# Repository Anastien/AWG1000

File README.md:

**AWG1000** is a an open source  (GPL-3.0 License) dual-channel arbitrary waveform generators with a 120MHz bandwidth, 1.2GSa/s sampling rate and 16-bit vertical resolution.

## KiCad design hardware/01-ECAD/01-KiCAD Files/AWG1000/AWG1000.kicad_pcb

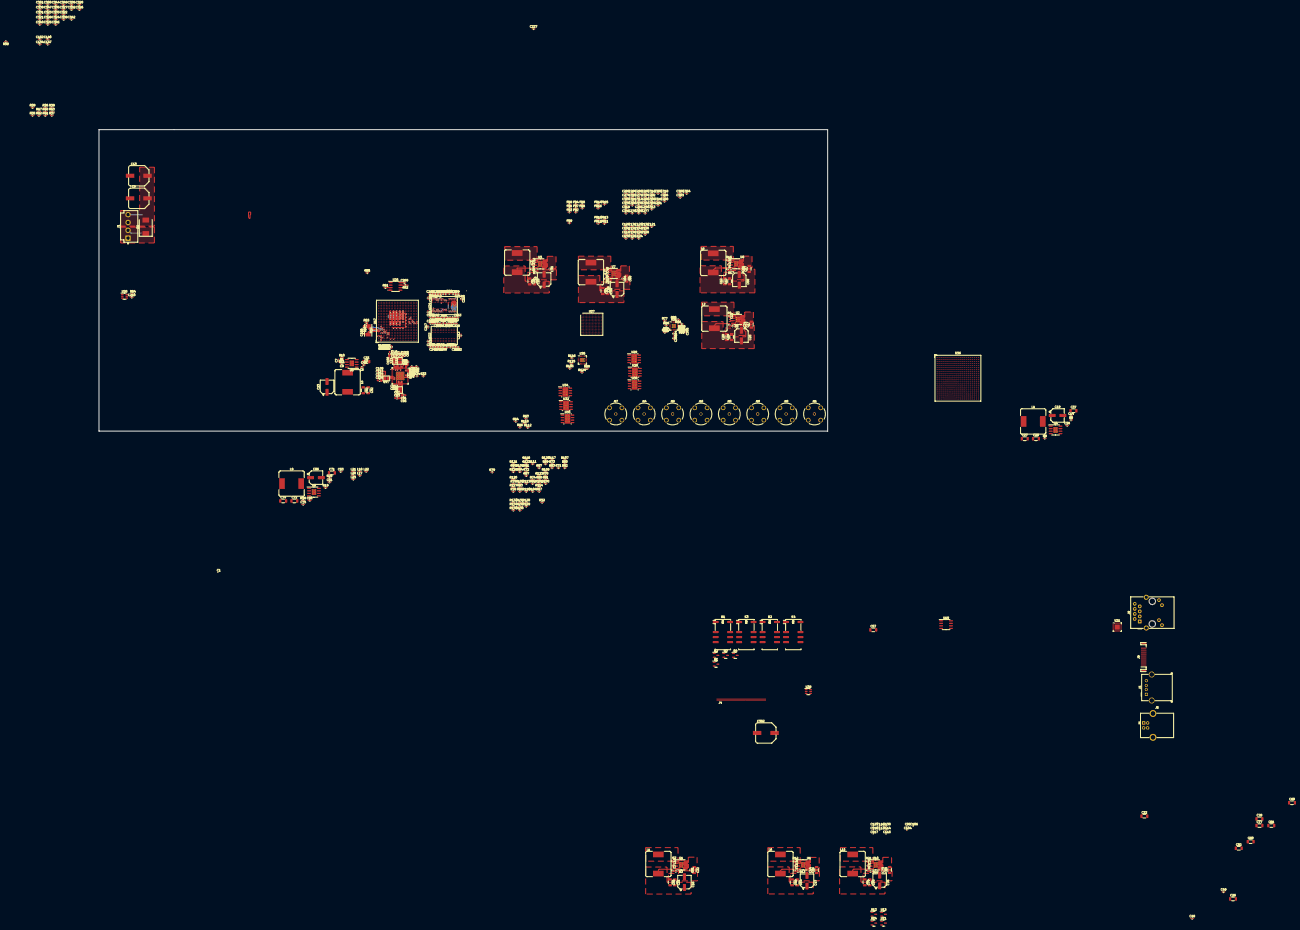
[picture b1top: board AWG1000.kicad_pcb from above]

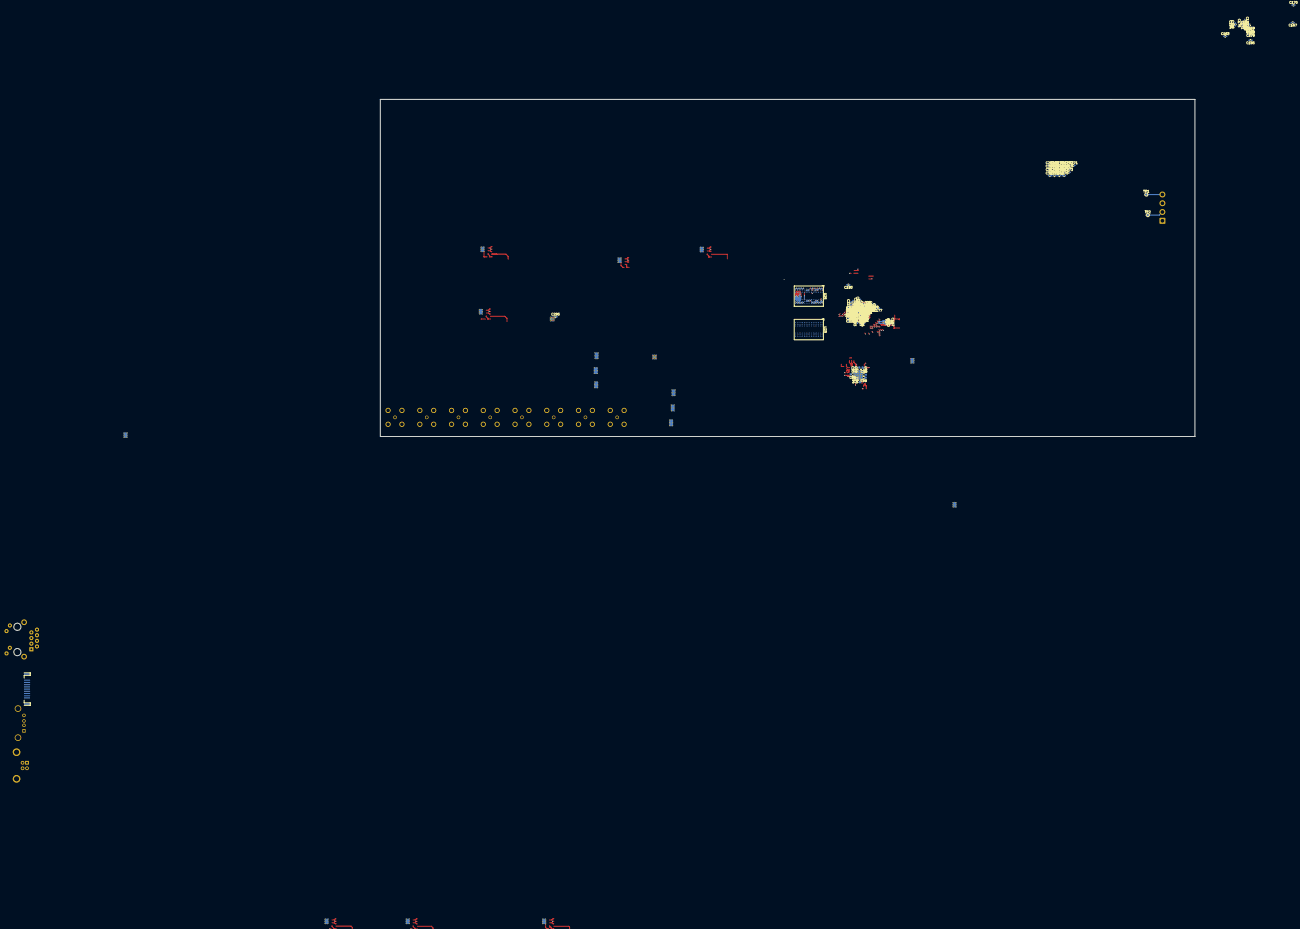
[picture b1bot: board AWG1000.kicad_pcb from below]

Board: 8 copper layers, 368.3 x 152.4 mm, 590 parts (113 on the bottom side), 374 nets.

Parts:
C1, C2, C3, C4, C15, C41, C45, C56, C95, C104, C106, C113, C114, C115, C116, C117, C118, C127, C130, C157, C158, C159, C164: 4.7uF; C0402_L
C6, C7, C9, C10, C11, C12, C14, C40, C49, C49#2, C49#3, C50, C51, C52, C53, C70: 0.47uF; R_0402_1005Metric_Pad0.72x0.64mm_HandSolder
C8, C13, C352: 220uF; EEE-FK1H221GP
C16, C18, C19, C20, C23, C47, C55, C58, C66, C76: 33uF; CP_Elec_6.3x7.7
C17, C21, C22, C22#2, C25, C26, C27, C28, C29, C30, C32, C33, C34, C36, C37, C39, C42, C48, C54, C57, C57#2, C59, C60, C62, C63, C65, C67, C68, C69, C71, C72, C74, C77, C78, C79, C80, C81, C82: 10uF; C_1206_3216Metric
C24, C31, C35, C38, C43, C44, C61, C64, C73, C75, C102, C109, C111, C112, C135, C136, C138, C139, C141, C142, C144, C145, C149, C150, C153, C154, C155, C156, C161, C162, C163, C165, C166, C168, C169, C171, C172, C174, C175, C178, C179, C180, C181, C182, C183, C184, C185, C190, C191, C192, C193, C194, C195, C196, C197, C198, C199, C200, C201, C202, C203, C204, C205, C206, C207, C208, C209, C210, C219, C220, C221, C222, C223, C224, C225, C226, C227, C228, C229, C230, C231, C232, C233, C234, C235, C236, C237, C238, C239, C240, C241, C242, C243, C244, C245, C246, C247, C248, C249, C250, C251, C252, C253, C254, C255, C256, C257, C258, C259, C260, C261, C262, C263, C264, C265, C266, C267, C268, C269, C270, C271, C272, C273, C275, C276, C287, C289, C290, C292, C293, C294, C296, C297, C310, C312, C317, C329, C343, C349: 220nF; R_0402_1005Metric_Pad0.72x0.64mm_HandSolder
C83, C84, C85, C86, C87, C88, C89, C90, C91, C92, C93, C94, C96, C97, C98, C99, C100, C101, C103, C105, C107, C108, C110: 22uF; C_0603_1608Metric_Pad1.08x0.95mm_HandSolder
C119, C120, C121, C122, C123, C124, C125, C126, C128, C129, C131, C132, C313, C353, C354, C355: 0.1uF; R_0402_1005Metric_Pad0.72x0.64mm_HandSolder
C133, C134, C140, C146, C147, C152, C160, C167, C170, C173, C176, C177, C186, C187, C188, C189, C211, C212, C213, C214, C215, C216, C217, C218, C295, C308, C320, C321, C322, C323, C324, C325, C326, C327, C328, C330, C331, C332, C333, C335, C336, C338, C340, C342, C344, C345, C347, C348, C350, C351: 22uF; R_0402_1005Metric_Pad0.72x0.64mm_HandSolder
C137, C143, C148, C151: 0.22uF; R_0402_1005Metric_Pad0.72x0.64mm_HandSolder
C274, C298: 9.1pF; R_0402_1005Metric_Pad0.72x0.64mm_HandSolder
C277, C302, C305, C337: 27pF; R_0402_1005Metric_Pad0.72x0.64mm_HandSolder
C278, C279, C280, C281, C282, C283, C299, C300, C303, C304, C306, C307: 10uF; R_0402_1005Metric_Pad0.72x0.64mm_HandSolder
C284, C288, C309, C311, C314, C318, C341, C346: 10nF; R_0402_1005Metric_Pad0.72x0.64mm_HandSolder
C285, C286, C315, C316: 4.5pF; R_0402_1005Metric_Pad0.72x0.64mm_HandSolder
C291, C319: 3.2pF; R_0402_1005Metric_Pad0.72x0.64mm_HandSolder
C301, C334: 8.2pF; R_0402_1005Metric_Pad0.72x0.64mm_HandSolder
C339: 0; R_0402_1005Metric_Pad0.72x0.64mm_HandSolder
D1: D_TVS; D_SMC
FB1, FB2, FB3, FB4, FB5, FB6, FB7, FB8, FB9, FB10, FB11, FB12, FB13, FB14, FB15, FB16: FerriteBead; L_0402_1005Metric_Pad0.77x0.64mm_HandSolder
J1: B4P-VH(LF)(SN); JST_VH_B4P-VH_1x04_P3.96mm_Vertical
J3: USB1040-GF-L-B; USB_A_Molex_67643_Horizontal
J4: TF31-50S-0.5SH(800)
J5: USB_B; USB_B_OST_USB-B1HSxx_Horizontal
J8: HDMI_A; HDMI_A_Contact_Technology_HDMI-19APL2_Horizontal
J9: RJ45_Amphenol_RJMG1BD3B8K1ANR
J11, J12, J13, J14, J15, J16, J17, J18: 5-1634503-1
K1, K2, K3, K4: EE2-5NU; Relay_DPDT_Kemet_EE2_NU
L1, L2, L3, L4, L5, L6, L7, L8, L9, L10: 47uH; L_Bourns_SRR1260
L12, L13, L14, L15: 1uH; 74404024010
L17, L18, L21, L22: 30nH; L_0402_1005Metric_Pad0.77x0.64mm_HandSolder
L20, L23: 56nH; L_0402_1005Metric_Pad0.77x0.64mm_HandSolder
Q1, Q2, Q3, Q4: BSN20; SOT-23
R1, R18, R23, R24, R25, R26, R27, R28, R29, R30, R31, R32, R33, R34, R88, R89, R95, R96, R98, R100, R117, R118, R120, R121, R122, R124: 0; R_0402_1005Metric_Pad0.72x0.64mm_HandSolder
R2, R4, R6, R8, R12, R14, R16, R21: 100k; R_0402_1005Metric_Pad0.72x0.64mm_HandSolder
R3, R5, R7, R9, R10, R11, R13, R15, R19, R20: 7.15k; R_0402_1005Metric_Pad0.72x0.64mm_HandSolder
R17, R22: 16.5k; R_0402_1005Metric_Pad0.72x0.64mm_HandSolder
R35, R36, R37, R38, R39, R40, R41, R42, R43, R44, R45, R46, R47, R48, R49, R50, R51, R52, R53, R54, R55, R61, R62, R65, R75, R76, R77, R86, R87, R93, R94, R102, R103, R104, R105, R113, R114, R115, R116, R119, R126, R128, R129, R130, R131, R132, R133, R134, R135: 49.9; R_0402_1005Metric_Pad0.72x0.64mm_HandSolder
R56, R57, R58, R59, R60: 240; R_0402_1005Metric_Pad0.72x0.64mm_HandSolder
R63, R64, R78, R79: 1k; R_0402_1005Metric_Pad0.72x0.64mm_HandSolder
R66, R67, R69, R70, R71, R82, R83, R90, R91, R92: 10k; R_0402_1005Metric_Pad0.72x0.64mm_HandSolder
R68, R97, R99, R123: 150; R_0402_1005Metric_Pad0.72x0.64mm_HandSolder
R72, R73, R74: 20; R_0402_1005Metric_Pad0.72x0.64mm_HandSolder
R80, R81, R84, R107, R108, R109: 30; R_0402_1005Metric_Pad0.72x0.64mm_HandSolder
R85, R111: 40.2; R_0402_1005Metric_Pad0.72x0.64mm_HandSolder
R101, R125: 249; R_0402_1005Metric_Pad0.72x0.64mm_HandSolder
R106, R127: 162; R_0402_1005Metric_Pad0.72x0.64mm_HandSolder
R110: 1.27k; R_0402_1005Metric_Pad0.72x0.64mm_HandSolder
R112: 10; R_0402_1005Metric_Pad0.72x0.64mm_HandSolder
TP1, TP2: TestPoint; TestPoint_Pad_D1.0mm
U1, U2, U3, U4, U6, U7, U8, U10: LMR23610ADDA; SOIC-8-1EP_3.9x4.9mm_P1.27mm_EP2.29x3mm_ThermalVias
U5, U9: TPS54531DDA; SOIC-8-1EP_3.9x4.9mm_P1.27mm_EP2.29x3mm_ThermalVias
U11, U12: MCP1702T-3302E_CB; SOT-23
U13, U14: MCP1702T-1202E_CB; SOT-23
U16: MMPF0100F3ANES; QFN-56-1EP_8x8mm_P0.5mm_EP4.3x4.3mm_ThermalVias
U17: MCIMX6S8DVM10AD; BGA-625_21.0x21.0mm_Layout25x25_P0.8mm
U19: MIC2025-2YM; SOIC-8_3.9x4.9mm_P1.27mm
U20: TPS3808G09DBVRG4; SOT-23-6
U21: LAN8720A; QFN-24-1EP_4x4mm_P0.5mm_EP2.6x2.6mm
U22, U23, U24, U25: AS4C256M16D3LC-12BCN; BGA-96_9.0x13.0mm_Layout2x3x16_P0.8mm
U26: W25Q32JWSSIQ; SOIC-8_3.9x4.9mm_P1.27mm
U27: DAC3482IZAYR; Microchip_TFBGA-196_11x11mm_Layout14x14_P0.75mm_SMD
U28, U29, U30, U32, U33, U34: THS3095; Texas_R-PDSO-G8_EP2.95x4.9mm_Mask2.4x3.1mm_ThermalVias
U31, U35: THS3217IRGVT; QFN-16-1EP_4x4mm_P0.65mm_EP2.1x2.1mm_ThermalVias
U36: LFE3-35EA-7FN484I; BGA-484_23.0x23.0mm_Layout22x22_P1.0mm
U38: SRV05-4; SOT-23-6
Y2: 32.768kHz; Crystal_SMD_2012-2Pin_2.0x1.2mm
Y3: 24MHz; Crystal_SMD_Abracon_ABM7-2Pin_6.0x3.5mm

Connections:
1: R63.1, R64.1, R78.1, R79.1
1.2V_DAC: U13.2 (VOUT), U27.E5 (DIGVDD), U27.E6 (DIGVDD), U27.E7 (DIGVDD), U27.F5 (DIGVDD), U27.J5 (DIGVDD), U27.L9 (DACVDD)
1.2V_DAC_CLK: C330.1, C332.1, U14.2 (VOUT), U27.K9 (DACVDD)
1.2V_DAC_DVDD: C55.1, C59.2, C63.2, L4.2, L7.2, R8.1, R14.1, U27.D1 (D10N), U27.E1 (D9N), U27.F1 (D8N), U27.J1 (D7N), U27.K1 (D6N), U27.L1 (D5N), U27.M1 (D4N), U27.P1 (D3N)
1.2V_DAC_VDD: U27.P2 (D2N), U27.P3 (D1N), U27.P4 (D0N)
1.5V_DDR: C83.2, C87.2, C91.2, C96.2, C111.1, C211.1, C212.2, C213.1, C214.2, C215.1, C216.2, C217.1, C218.2, C219.1, C220.2, C221.1, C222.2, C223.1, C224.2, C225.1, C226.2, C227.1, C228.2, C229.1, C230.2, C231.1, C232.2, C233.1, C234.2, C235.1, C236.2, C237.1, C238.2, C239.1, C240.2, C241.1, C242.2, C243.1, C244.2, C245.1, C246.2, C247.1, C248.2, C249.1, C250.2, C251.1, C252.2, C253.1, C254.2, C255.1, C256.2, C257.1, C258.2, C259.1, C260.2, C261.1, C262.2, C263.1, C264.2, C265.1, C266.2, C267.1, C268.2, L15.2, U16.30 (VINREFDDR), U16.38 (SW3AFB), U17.R18 (NVCC_DRAM_1), U17.T18 (NVCC_DRAM_2), U17.U18 (NVCC_DRAM_3), U17.V9 (NVCC_DRAM_13), U17.V10 (NVCC_DRAM_4), U17.V11 (NVCC_DRAM_5), U17.V12 (NVCC_DRAM_6), U17.V13 (NVCC_DRAM_7), U17.V14 (NVCC_DRAM_8), U17.V15 (NVCC_DRAM_9), U17.V16 (NVCC_DRAM_10), U17.V17 (NVCC_DRAM_11), U17.V18 (NVCC_DRAM_12), U22.A1 (VDDQ), U22.A8 (VDDQ), U22.B2 (VDD), U22.C1 (VDDQ), U22.C9 (VDDQ), U22.D2 (VDDQ), U22.D9 (VDD), U22.E9 (VDDQ), U22.F1 (VDDQ), U22.G7 (VDD), U22.H2 (VDDQ), U22.H9 (VDDQ), U22.K2 (VDD), U22.K8 (VDD), U22.N1 (VDD), U22.N9 (VDD), U22.R1 (VDD), U22.R9 (VDD), U23.A1 (VDDQ), U23.A8 (VDDQ), U23.B2 (VDD), U23.C1 (VDDQ), U23.C9 (VDDQ), U23.D2 (VDDQ), U23.D9 (VDD), U23.E9 (VDDQ), U23.F1 (VDDQ), U23.G7 (VDD), U23.H2 (VDDQ), U23.H9 (VDDQ), U23.K2 (VDD), U23.K8 (VDD), U23.N1 (VDD), U23.N9 (VDD), U23.R1 (VDD), U23.R9 (VDD), U24.A1 (VDDQ), U24.A8 (VDDQ), U24.B2 (VDD), U24.C1 (VDDQ), U24.C9 (VDDQ), U24.D2 (VDDQ), U24.D9 (VDD), U24.E9 (VDDQ), U24.F1 (VDDQ), U24.G7 (VDD), U24.H2 (VDDQ), U24.H9 (VDDQ), U24.K2 (VDD), U24.K8 (VDD), U24.N1 (VDD), U24.N9 (VDD), U24.R1 (VDD), U24.R9 (VDD), U25.A1 (VDDQ), U25.A8 (VDDQ), U25.B2 (VDD), U25.C1 (VDDQ), U25.C9 (VDDQ), U25.D2 (VDDQ), U25.D9 (VDD), U25.E9 (VDDQ), U25.F1 (VDDQ), U25.G7 (VDD), U25.H2 (VDDQ), U25.H9 (VDDQ), U25.K2 (VDD), U25.K8 (VDD), U25.N1 (VDD), U25.N9 (VDD), U25.R1 (VDD), U25.R9 (VDD)
1.8V_SW: C108.2, C110.2
3.3V_DAC_AN: C320.1, C321.1, C322.1, C323.1, C324.1, C325.1, C326.1, C327.1, C328.1, C333.1, C335.1, C336.1, C338.1, C340.1, C342.1, C344.1, C347.1, C350.1, U11.2 (VOUT), U27.D5 (IOVDD), U27.D6 (IOVDD), U27.D9 (DACVDD), U27.E9 (DACVDD), U27.G5 (IOVDD), U27.H5 (IOVDD), U27.L5 (IOVDD), U27.L6 (IOVDD)
3.3V_DAC_IO: U12.2 (VOUT), U27.A11 (DACCLKN), U27.B5 (SYNCN), U27.B9 (OSTRN), U27.G1 (DATACLKN), U27.H1 (FRAMEN), U27.P5 (PARITYN)
3.3V_SW: C23.1, C32.2, C42.2, C85.2, C86.1, C89.2, C90.1, C93.2, C94.1, C98.2, C99.1, L5.2, R10.1, R23.1, R30.2, R31.2, U16.7 (SW1AIN), U16.10 (SW1BIN), U16.12 (SW1CIN), U16.17 (VIN1), U16.23 (SW2IN_1), U16.24 (SW2IN_2), U16.27 (VIN2), U16.34 (SW3BIN), U16.37 (SW3AIN), U16.40 (VIN3), U16.50 (VIN)
3.3V_SW_DELAYED: C66.1, C71.2, C74.2, C176.1, C177.2, C178.1, C179.2, C180.1, C181.2, C182.1, C183.2, C184.1, C185.2, C210.1, C269.1, L9.2, R19.1, R45.1, R46.1, R47.1, R54.2, R61.1, R62.1, U16.55 (VDDIO), U17.G14 (NVCC_SD3), U17.G15 (NVCC_NANDF), U17.G16 (NVCC_SD1), U17.G17 (NVCC_SD2), U17.J7 (NVCC_JTAG), U17.K19 (NVCC_EIM0), U17.L19 (NVCC_EIM1), U17.M19 (NVCC_EIM2), U17.N7 (NVCC_CSI), U17.P7 (NVCC_GPIO), U17.P19 (NVCC_LCD), U17.R19 (NVCC_ENET), U20.6 (VDD), U26.8 (VCC)
3V0_STBY: C175.1, U16.43 (VSNVS), U17.G11 (VDD_SNVS_IN)
3V_VDDHIGH: C105.2, C107.2, C173.1, C174.1, L14.1, U16.25 (SW2FB), U17.H9 (VDDHIGH_IN_1), U17.J9 (VDDHIGH_IN_2)
5V_SW_DELAYED: C140.1, C143.1, U17.D10 (USB_H1_VBUS), U19.7 (IN)
3095_1_EN: U28.8 (~PD), U29.8 (~PD), U30.8 (~PD)
3095_1_OUT: J15.1 (In), R85.1
3095_2_EN: U32.8 (~PD), U33.8 (~PD), U34.8 (~PD)
3095_2_OUT: J16.1 (In), R111.1
+3.3V_CLK: FB1.1, FB2.1, FB3.1, FB4.1, FB5.1, FB6.1, FB7.1, FB8.1, R35.2, R37.2, R41.1, R42.1
+7V: C76.1, C79.2, C80.2, C284.1, C287.1, C314.1, C317.1, FB10.1, FB12.1, L10.2, R21.1, R89.2, R118.2, U31.13 (+VCC1)
+15V: C47.1, C48.2, C54.2, C270.1, C271.2, C272.1, C273.2, C275.1, C276.2, C278.1, C279.2, C280.1, C281.2, C282.1, C283.2, L6.2, R12.1, U28.7 (VS+), U29.7 (VS+), U30.7 (VS+), U32.7 (VS+), U33.7 (VS+), U34.7 (VS+)
+VREF_DDR: U16.31 (VREFDDR), U17.AC2 (DRAM_VREF), U22.H1 (VREFDQ), U22.M8 (VREFCA), U23.H1 (VREFDQ), U23.M8 (VREFCA), U24.H1 (VREFDQ), U24.M8 (VREFCA), U25.H1 (VREFDQ), U25.M8 (VREFCA)
-7V: C45.1, C58.1, C62.2, C67.2, C309.1, C310.1, C341.1, C343.1, FB11.1, FB13.1, R17.1, U8.6 (AGND), U8.8 (PGND), U8.9 (PAD), U31.8 (-VCC1), U35.8 (-VCC1)
-15V: C1.1, C20.1, C29.2, C39.2, C289.1, C290.2, C293.1, C294.2, C296.1, C297.2, C299.1, C300.2, C303.1, C304.2, C306.1, C307.2, R5.1, U2.6 (AGND), U2.8 (PGND), U2.9 (PAD), U28.4 (VS-), U29.4 (VS-), U30.4 (VS-), U32.1 (REF), U33.1 (REF), U34.1 (REF)
/DAC/3217_1_out: R65.2, R101.2, U31.11 (VOUT)
/DAC/IOUT1_N: C286.1, C316.1, L18.1, L22.1, R77.2, R114.2
/DAC/IOUT1_P: C285.2, C315.2, L17.1, L21.1, R76.1, R113.1
/DAC/PLLAVDD: C345.1, C348.1, C351.1, U27.K5 (DIGVDD), U27.K6 (DIGVDD)
/DAC/RF1+: K2.4, R84.2, U28.6 (VOUT)
/DAC/RF1-: K2.9, R75.2, U28.2 (VIN-), U29.2 (VIN-), U30.2 (VIN-)
/DAC/RF2+: K4.4, R107.2, U32.6 (VOUT)
/DAC/RF2-: K4.9, R105.2, U32.2 (VIN-), U33.2 (VIN-), U34.2 (VIN-)
/DAC/THS3217_2_N: C346.1, C349.1, FB13.2
/DAC/THS3217_2_P: C318.1, C329.1, FB12.2, U35.5 (-VCC2), U35.16 (+VCC2)
/DAC/THS3217_I_N: C311.1, C312.1, FB11.2
/DAC/THS3217_I_P: C288.1, C292.1, FB10.2, U31.5 (-VCC2), U31.16 (+VCC2)
/INTERFACE/VBUS: C352.1, C354.1, FB15.1, J3.1 (VBUS), U38.5 (VP)
/MEMORY/DRAM_A0: U17.AC14 (DRAM_A0), U22.N3 (A0), U23.N3 (A0), U24.N3 (A0), U25.N3 (A0)
/MEMORY/DRAM_A1: U17.AB14 (DRAM_A1), U22.P7 (A1), U23.P7 (A1), U24.P7 (A1), U25.P7 (A1)
/MEMORY/DRAM_A2: U17.AA14 (DRAM_A2), U22.P3 (A2), U23.P3 (A2), U24.P3 (A2), U25.P3 (A2)
/MEMORY/DRAM_A3: U17.Y14 (DRAM_A3), U22.N2 (A3), U23.N2 (A3), U24.N2 (A3), U25.N2 (A3)
/MEMORY/DRAM_A4: U17.W14 (DRAM_A4), U22.P8 (A4), U23.P8 (A4), U24.P8 (A4), U25.P8 (A4)
/MEMORY/DRAM_A5: U17.AE13 (DRAM_A5), U22.P2 (A5), U23.P2 (A5), U24.P2 (A5), U25.P2 (A5)
/MEMORY/DRAM_A6: U17.AC13 (DRAM_A6), U22.R8 (A6), U23.R8 (A6), U24.R8 (A6), U25.R8 (A6)
/MEMORY/DRAM_A7: U17.Y13 (DRAM_A7), U22.R2 (A7), U23.R2 (A7), U24.R2 (A7), U25.R2 (A7)
/MEMORY/DRAM_A8: U17.AB13 (DRAM_A8), U22.T8 (A8), U23.T8 (A8), U24.T8 (A8), U25.T8 (A8)
/MEMORY/DRAM_A9: U17.AE12 (DRAM_A9), U22.R3 (A9), U23.R3 (A9), U24.R3 (A9), U25.R3 (A9)
/MEMORY/DRAM_A10: U17.AA15 (DRAM_A10), U22.L7 (A10/AP), U23.L7 (A10/AP), U24.L7 (A10/AP), U25.L7 (A10/AP)
/MEMORY/DRAM_A11: U17.AC12 (DRAM_A11), U22.R7 (A11), U23.R7 (A11), U24.R7 (A11), U25.R7 (A11)
/MEMORY/DRAM_A12: U17.AD12 (DRAM_A12), U22.N7 (A12/~BC), U23.N7 (A12/~BC), U24.N7 (A12/~BC), U25.N7 (A12/~BC)
/MEMORY/DRAM_A13: U17.AC17 (DRAM_A13), U22.T3 (A13), U23.T3 (A13), U24.T3 (A13), U25.T3 (A13)
/MEMORY/DRAM_A14: U17.AA12 (DRAM_A14), U22.T7 (A14), U23.T7 (A14), U24.T7 (A14), U25.T7 (A14)
/MEMORY/DRAM_CAS_B: U17.AE16 (DRAM_CAS), U22.K3 (~CAS), U23.K3 (~CAS), U24.K3 (~CAS), U25.K3 (~CAS)
/MEMORY/DRAM_CLK1_N: U17.AE14 (~DRAM_SDCLK1), U22.K7 (~CK), U23.K7 (~CK), U24.K7 (~CK), U25.K7 (~CK)
/MEMORY/DRAM_CLK1_P: U17.AD14 (DRAM_SDCLK_1), U22.J7 (CK), U23.J7 (CK), U24.J7 (CK), U25.J7 (CK)
/MEMORY/DRAM_CS0_B: U17.Y16 (DRAM_CS0), U22.L2 (~CS), U23.L2 (~CS), U24.L2 (~CS), U25.L2 (~CS)
/MEMORY/DRAM_D0: U17.AD2 (DRAM_D0), U22.E3 (DQ0)
/MEMORY/DRAM_D1: U17.AE2 (DRAM_D1), U22.H3 (DQ4)
/MEMORY/DRAM_D2: U17.AC4 (DRAM_D2), U22.H7 (DQ7)
/MEMORY/DRAM_D3: U17.AA5 (DRAM_D3), U22.F8 (DQ3)
/MEMORY/DRAM_D4: U17.AC1 (DRAM_D4), U22.F2 (DQ2)
/MEMORY/DRAM_D5: U17.AD1 (DRAM_D5), U22.G2 (DQ6)
/MEMORY/DRAM_D6: U17.AB4 (DRAM_D6), U22.F7 (DQ1)
/MEMORY/DRAM_D7: U17.AE4 (DRAM_D7), U22.H8 (DQ5)
/MEMORY/DRAM_D8: U17.AD5 (DRAM_D8), U22.D7 (DQ8)
/MEMORY/DRAM_D9: U17.AE5 (DRAM_D9), U22.C3 (DQ9)
/MEMORY/DRAM_D10: U17.AA6 (DRAM_D10), U22.B8 (DQ14)
/MEMORY/DRAM_D11: U17.AE7 (DRAM_D11), U22.C8 (DQ10)
/MEMORY/DRAM_D12: U17.AB5 (DRAM_D12), U22.C2 (DQ11)
/MEMORY/DRAM_D13: U17.AC5 (DRAM_D13), U22.A3 (DQ15)
/MEMORY/DRAM_D14: U17.AB6 (DRAM_D14), U22.A2 (DQ13)
/MEMORY/DRAM_D15: U17.AC7 (DRAM_D15), U22.A7 (DQ12)
/MEMORY/DRAM_D16: U17.AB7 (DRAM_D16), U23.E3 (DQ0)
/MEMORY/DRAM_D17: U17.AA8 (DRAM_D17), U23.F7 (DQ1)
/MEMORY/DRAM_D18: U17.AB9 (DRAM_D18), U23.H3 (DQ4)
/MEMORY/DRAM_D19: U17.Y9 (DRAM_D19), U23.H8 (DQ5)
/MEMORY/DRAM_D20: U17.Y7 (DRAM_D20), U23.G2 (DQ6)
/MEMORY/DRAM_D21: U17.Y8 (DRAM_D21), U23.F8 (DQ3)
/MEMORY/DRAM_D22: U17.AC8 (DRAM_D22), U23.F2 (DQ2)
/MEMORY/DRAM_D23: U17.AA9 (DRAM_D23), U23.H7 (DQ7)
/MEMORY/DRAM_D24: U17.AE9 (DRAM_D24), U23.D7 (DQ8)
/MEMORY/DRAM_D25: U17.Y10 (DRAM_D25), U23.A2 (DQ13)
/MEMORY/DRAM_D26: U17.AE11 (DRAM_D26), U23.B8 (DQ14)
/MEMORY/DRAM_D27: U17.AB11 (DRAM_D27), U23.C2 (DQ11)
/MEMORY/DRAM_D28: U17.AC9 (DRAM_D28), U23.C3 (DQ9)
/MEMORY/DRAM_D29: U17.AD9 (DRAM_D29), U23.A7 (DQ12)
/MEMORY/DRAM_D30: U17.AD11 (DRAM_D30), U23.C8 (DQ10)
/MEMORY/DRAM_D31: U17.AC11 (DRAM_D31), U23.A3 (DQ15)
/MEMORY/DRAM_D32: U17.AA17 (DRAM_D32), U24.E3 (DQ0)
/MEMORY/DRAM_D33: U17.AA18 (DRAM_D33), U24.H3 (DQ4)
/MEMORY/DRAM_D34: U17.AC18 (DRAM_D34), U24.F7 (DQ1)
/MEMORY/DRAM_D35: U17.AE19 (DRAM_D35), U24.H7 (DQ7)
/MEMORY/DRAM_D36: U17.Y17 (DRAM_D36), U24.G2 (DQ6)
/MEMORY/DRAM_D37: U17.Y18 (DRAM_D37), U24.F2 (DQ2)
/MEMORY/DRAM_D38: U17.AB19 (DRAM_D38), U24.F8 (DQ3)
/MEMORY/DRAM_D39: U17.AC19 (DRAM_D39), U24.H8 (DQ5)
/MEMORY/DRAM_D40: U17.Y19 (DRAM_D40), U24.D7 (DQ8)
/MEMORY/DRAM_D41: U17.AB20 (DRAM_D41), U24.C2 (DQ11)
/MEMORY/DRAM_D42: U17.AB21 (DRAM_D42), U24.A7 (DQ12)
/MEMORY/DRAM_D43: U17.AD21 (DRAM_D43), U24.C8 (DQ10)
/MEMORY/DRAM_D44: U17.Y20 (DRAM_D44), U24.A2 (DQ13)
/MEMORY/DRAM_D45: U17.AA20 (DRAM_D45), U24.A3 (DQ15)
/MEMORY/DRAM_D46: U17.AE21 (DRAM_D46), U24.B8 (DQ14)
/MEMORY/DRAM_D47: U17.AC21 (DRAM_D47), U24.C3 (DQ9)
/MEMORY/DRAM_D48: U17.AC22 (DRAM_D48), U25.E3 (DQ0)
/MEMORY/DRAM_D49: U17.AE22 (DRAM_D49), U25.G2 (DQ6)
/MEMORY/DRAM_D50: U17.AE24 (DRAM_D50), U25.H7 (DQ7)
/MEMORY/DRAM_D51: U17.AC24 (DRAM_D51), U25.F8 (DQ3)
/MEMORY/DRAM_D52: U17.AB22 (DRAM_D52), U25.F2 (DQ2)
/MEMORY/DRAM_D53: U17.AC23 (DRAM_D53), U25.H3 (DQ4)
/MEMORY/DRAM_D54: U17.AD25 (DRAM_D54), U25.F7 (DQ1)
/MEMORY/DRAM_D55: U17.AC25 (DRAM_D55), U25.H8 (DQ5)
/MEMORY/DRAM_D56: U17.AD23 (DRAM_SDQS6), U25.D7 (DQ8)
/MEMORY/DRAM_D57: U17.AA21 (DRAM_D57), U25.C2 (DQ11)
/MEMORY/DRAM_D58: U17.Y25 (DRAM_D58), U25.B8 (DQ14)
/MEMORY/DRAM_D59: U17.Y22 (DRAM_D59), U25.A2 (DQ13)
/MEMORY/DRAM_D60: U17.AB23 (DRAM_D60), U25.C3 (DQ9)
/MEMORY/DRAM_D61: U17.AA23 (DRAM_D61), U25.A3 (DQ15)
/MEMORY/DRAM_D62: U17.Y23 (DRAM_D62), U25.A7 (DQ12)
/MEMORY/DRAM_D63: U17.W25 (DRAM_D63), U25.C8 (DQ10)
/MEMORY/DRAM_DQM0: U17.AC3 (DRAM_DQM0), U22.E7 (LDM)
/MEMORY/DRAM_DQM1: U17.AC6 (DRAM_DQM1), U22.D3 (UDM)
/MEMORY/DRAM_DQM2: U17.AB8 (DRAM_DQM2), U23.E7 (LDM)
/MEMORY/DRAM_DQM3: U17.AE10 (DRAM_DQM3), U23.D3 (UDM)
/MEMORY/DRAM_DQM4: U17.AB18 (DRAM_DQM4), U24.E7 (LDM)
/MEMORY/DRAM_DQM5: U17.AC20 (DRAM_DQM5), U24.D3 (UDM)
/MEMORY/DRAM_DQM6: U17.AB25 (DRAM_D56), U25.E7 (LDM)
/MEMORY/DRAM_DQM7: U17.Y21 (DRAM_DQM7), U25.D3 (UDM)
/MEMORY/DRAM_DQS0_N: U17.AD3 (~DRAM_SDQS0), U22.G3 (~LDQS)
/MEMORY/DRAM_DQS0_P: U17.AE3 (DRAM_SDQS0), U22.F3 (LDQS)
/MEMORY/DRAM_DQS1_N: U17.AE6 (~DRAM_SDQS1), U22.B7 (~UDQS)
/MEMORY/DRAM_DQS1_P: U17.AD6 (DRAM_SDQS1), U22.C7 (UDQS)
/MEMORY/DRAM_DQS2_P: U17.AD8 (DRAM_SDQS2), U17.AE8 (~DRAM_SDQS2), U23.F3 (LDQS), U23.G3 (~LDQS)
/MEMORY/DRAM_DQS3_N: U17.AB10 (~DRAM_SDQS3), U23.B7 (~UDQS)
/MEMORY/DRAM_DQS3_P: U17.AC10 (DRAM_SDQS3), U23.C7 (UDQS)
/MEMORY/DRAM_DQS4_N: U17.AE18 (~DRAM_SDQS4), U24.G3 (~LDQS)
/MEMORY/DRAM_DQS4_P: U17.AD18 (DRAM_SDQS4), U24.F3 (LDQS)
/MEMORY/DRAM_DQS5_N: U17.AE20 (~DRAM_SDQS5), U24.B7 (~UDQS)
/MEMORY/DRAM_DQS5_P: U17.AD20 (DRAM_SDQS5), U24.C7 (UDQS)
/MEMORY/DRAM_DQS6_N: U17.AD24 (DRAM_DQM6), U25.G3 (~LDQS)
/MEMORY/DRAM_DQS6_P: U17.AE23 (~DRAM_SDQS6), U25.F3 (LDQS)
/MEMORY/DRAM_DQS7_N: U17.AA24 (~DRAM_SDQS7), U25.B7 (~UDQS)
/MEMORY/DRAM_DQS7_P: U17.AA25 (DRAM_SDQS7), U25.C7 (UDQS)
/MEMORY/DRAM_RAS_B: U17.AB15 (DRAM_RAS), U22.J3 (~RAS), U23.J3 (~RAS), U24.J3 (~RAS), U25.J3 (~RAS)
/MEMORY/DRAM_RESET_B: U17.Y6 (DRAM_RESET), U22.T2 (~RESET), U23.T2 (~RESET), U24.T2 (~RESET), U25.T2 (~RESET)
/MEMORY/DRAM_SDBA0: U17.AC15 (DRAM_SDBA0), U22.M2 (BA0), U23.M2 (BA0), U24.M2 (BA0), U25.M2 (BA0)
/MEMORY/DRAM_SDBA1: U17.Y15 (DRAM_SDBA1), U22.N8 (BA1), U23.N8 (BA1), U24.N8 (BA1), U25.N8 (BA1)
/MEMORY/DRAM_SDBA2: U17.AB12 (DRAM_SDBA2), U22.M3 (BA2), U23.M3 (BA2), U24.M3 (BA2), U25.M3 (BA2)
/MEMORY/DRAM_SDCKE0: U17.Y11 (DRAM_SDCKE0), U22.K9 (CKE), U23.K9 (CKE), U24.K9 (CKE), U25.K9 (CKE)
/MEMORY/DRAM_SDODT0: U17.AC16 (DRAM_SDODT0), U22.K1 (ODT), U23.K1 (ODT), U24.K1 (ODT), U25.K1 (ODT)
/MEMORY/DRAM_WE_B: U17.AB16 (DRAM_SDWE), U22.L3 (~WE), U23.L3 (~WE), U24.L3 (~WE), U25.L3 (~WE)
/MPU/DAC_CLK_N: C131.1, R40.2, R41.2, R42.2
/MPU/DAC_CLK_P: C132.1, R39.2
/MPU/IMX_RST: R54.1, U17.C11 (~POR), U20.1 (~RESET)
/MPU/JTAG_MOD: R48.2, U17.H6 (JTAG_MOD)
/MPU/JTAG_TCK_B: R49.2, U17.H5 (JTAG_TCK)
/MPU/JTAG_TDI_B: R46.2, R50.2, U17.G5 (JTAG_TDI)
/MPU/JTAG_TDO_B: R51.2, U17.G6 (JTAG_TDO)
/MPU/NVCC_PLL_OUT: C170.2, C172.2, U17.E8 (NVCC_PLL_OUT)
/MPU/RTC_I: C158.1, R44.2, U17.D9 (RTC_XTALI), Y2.2
/MPU/RTC_O: C157.1, R44.1, U17.C9 (RTC_XTALO), Y2.1
/MPU/SEC_CLK: C126.2, R35.1, R36.1
/MPU/VDDUSB_CAP: C134.1, C137.1, U17.F9 (VDDUSB_CAP)
/MPU/VDD_ARM_CAP: C133.1, C135.1, C136.2, C138.1, C139.2, C141.1, C142.2, C144.1, C145.2, U17.H11 (VDDARM23_CAP_1), U17.H13 (VDDARM_CAP_1), U17.J11 (VDDARM23_CAP_2), U17.J13 (VDDARM_CAP_2), U17.K11 (VDDARM23_CAP_3), U17.K13 (VDDARM_CAP_3), U17.L11 (VDDARM23_CAP_4), U17.L13 (VDDARM_CAP_4), U17.M11 (VDDARM23_CAP_5), U17.M13 (VDDARM_CAP_5), U17.N11 (VDDARM23_CAP_6), U17.N13 (VDDARM_CAP_6), U17.P11 (VDDARM23_CAP_7), U17.P13 (VDDARM_CAP_7), U17.R11 (VDDARM23_CAP_8), U17.R13 (VDDARM_CAP_8)
/MPU/VDD_HIGH_CAP: C167.1, C168.2, C169.1, U17.H10 (VDDHIGH_CAP_1), U17.J10 (VDDHIGH_CAP_2), U17.K7 (NVCC_MIPI)
/MPU/VDD_PU_CAP: C160.1, C161.2, C162.1, C163.2, C165.1, C166.2, U17.H17 (VDDPU_CAP_1), U17.J17 (VDDPU_CAP_2), U17.K17 (VDDPU_CAP_3), U17.L17 (VDDPU_CAP_4), U17.M17 (VDDPU_CAP_5), U17.N17 (VDDPU_CAP_6), U17.P17 (VDDPU_CAP_7)
/MPU/VDD_SNVS_CAP: C171.1, U17.G9 (VDD_SNVS_CAP)
/MPU/VDD_SOC_CAP: C146.1, C149.1, C150.2, C153.1, C154.2, C155.1, C156.2, U17.R10 (VDDSOC_CAP_1), U17.T10 (VDDSOC_CAP_2), U17.T13 (VDDSOC_CAP_3), U17.T14 (VDDSOC_CAP_4), U17.U10 (VDDSOC_CAP_5), U17.U13 (VDDSOC_CAP_6), U17.U14 (VDDSOC_CAP_7)
/MPU/XTAL_I: C164.1, R52.2, R53.2, U17.A7 (XTALI), Y3.2
/MPU/XTAL_O: C159.1, R52.1, U17.B7 (XTALO), Y3.1
/Power Mangement/2.5V_FPGA: C18.1, C25.2, C34.2, L3.2, R6.1
/Power Mangement/3.6V: C16.1, C21.2, C30.2, L1.2, R2.1, U11.3 (VIN), U12.3 (VIN), U13.3 (VIN), U14.3 (VIN)
BKLT_N: J4.3 (LEDK), J4.4 (LEDK)
BKLT_P: J4.1 (LEDA), J4.2 (LEDA)
BOOT_M0: R131.1, U17.C12 (BOOT_MODE0)
BOOT_M1: R130.1, U17.F12 (BOOT_MODE1)
CDC-PRIREF+: C355.1, R133.2, R134.1
DACCLK_N: C131.2, R43.2, U27.D7 (VFUSE), U27.H12 (BIASJ)
DACCLK_P: C132.2, R43.1
ETH_RX_N: J9.R3 (RD+), U21.22 (RXN)
ETH_RX_P: J9.R6 (RD-), U21.23 (RXP)
ETH_TX_N: J9.R2 (TD-), U21.20 (TXN)
ETH_TX_P: J9.R1 (TD+), U21.21 (TXP)
GND: C2.1, C3.1, C4.1, C7.2, C8.2, C9.2, C13.2, C15.1, C16.2, C17.1, C18.2, C19.2, C20.2, C21.1, C22.2, C22#2.2, C23.2, C24.1, C25.1, C26.2, C27.1, C28.2, C29.1, C30.1, C31.2, C32.1, C33.2, C34.1, C35.2, C36.1, C37.1, C38.2, C39.1, C41.1, C42.1, C43.2, C44.1, C47.2, C48.1, C51.2, C53.2, C54.1, C55.2, C56.1, C57.1, C57#2.1, C58.2, C59.1, C60.2, C61.1, C62.1, C63.1, C64.2, C65.1, C66.2, C67.1, C71.1, C72.2, C73.1, C74.1, C75.2, C76.2, C79.1, C80.1, C83.1, C84.1, C85.1, C86.2, C87.1, C88.1, C89.1, C90.2, C91.1, C92.1, C93.1, C94.2, C95.2, C96.1, C97.1, C98.1, C99.2, C100.1, C101.1, C102.1, C103.1, C104.2, C105.1, C106.2, C107.1, C108.1, C109.2, C110.1, C112.2, C113.2, C114.2, C115.2, C116.2, C117.2, C118.2, C119.2, C120.2, C121.2, C122.2, C123.2, C124.2, C125.2, C127.2, C128.2, C129.2, C130.2, C133.2, C134.2, C135.2, C136.1, C137.2, C138.2, C139.1, C140.2, C141.2, C142.1, C143.2, C144.2, C145.1, C146.2, C149.2, C150.1, C153.2, C154.1, C155.2, C156.1, C157.2, C158.2, C159.2, C160.2, C161.1, C162.2, C163.1, C164.2, C165.2, C166.1, C167.2, C168.1, C169.2, C170.1, C171.2, C172.1, C173.2, C174.2, C175.2, C176.2, C177.1, C178.2, C179.1, C180.2, C181.1, C182.2, C183.1, C184.2, C185.1, C186.2, C187.1, C188.2, C189.1, C190.2, C191.1, C192.2, C193.1, C194.2, C195.1, C196.2, C197.1, C198.2, C199.1, C200.2, C201.1, C202.2, C203.1, C204.2, C205.1, C206.2, C207.1, C208.2, C209.1, C210.2, C211.2, C212.1, C213.2, C214.1, C215.2, C216.1, C217.2, C218.1, C219.2, C220.1, C221.2, C222.1, C223.2, C224.1, C225.2, C226.1, C227.2, C228.1, C229.2, C230.1, C231.2, C232.1, C233.2, C234.1, C235.2, C236.1, C237.2, C238.1, C239.2, C240.1, C241.2, C242.1, C243.2, C244.1, C245.2, C246.1, C247.2, C248.1, C249.2, C250.1, C251.2, C252.1, C253.2, C254.1, C255.2, C256.1, C257.2, C258.1, C259.2, C260.1, C261.2, C262.1, C263.2, C264.1, C265.2, C266.1, C267.2, C268.1, C269.2, C270.2, C271.1, C272.2, C273.1, C274.2, C275.2, C276.1, C277.2, C278.2, C279.1, C280.2, C281.1, C282.2, C283.1, C284.2, C285.1, C286.2, C287.2, C288.2, C289.2, C290.1, C292.2, C293.2, C294.1, C295.1, C296.2, C297.1, C298.2, C299.2, C300.1, C301.2, C302.2, C303.2, C304.1, C305.2, C306.2, C307.1, C308.2, C309.2, C310.2, C311.2, C312.2, C313.1, C314.2, C315.1, C316.2, C317.2, C318.2, C320.2, C321.2, C322.2, C323.2, C324.2, C325.2, C326.2, C327.2, C328.2, C329.2, C330.2, C331.1, C332.2, C333.2, C334.2, C335.2, C336.2, C337.2, C338.2, C339.2, C340.2, C341.2, C342.2, C343.2, C344.2, C345.2, C346.2, C347.2, C348.2, C349.2, C350.2, C351.2, C352.2, C353.2, C354.2, D1.1 (A1), FB9.2, FB14.2, FB16.2, J1.1, J1.2, J3.4 (GND), J11.2 (Ext), J15.2 (Ext), J16.2 (Ext), L2.2, L8.2, Q1.2 (S), Q2.2 (S), Q3.2 (S), Q4.2 (S), R3.1, R4.1, R7.1, R9.1, R11.2, R13.1, R15.1, R16.1, R20.2, R22.1, R29.1, R32.1, R33.1, R36.2, R38.2, R39.1, R40.1, R53.1, R56.1, R57.1, R58.1, R59.1, R60.1, R66.2, R67.2, R68.2, R75.1, R76.2, R77.1, R82.2, R83.2, R86.1, R87.1, R88.2, R95.1, R97.2, R105.1, R106.1, R112.1, R113.2, R114.1, R115.1, R116.1, R117.2, R120.1, R127.1, R129.2, R130.2, R131.2, R132.2, R133.1, R135.1, TP2.1, U1.6 (AGND), U1.8 (PGND), U1.9 (PAD), U3.6 (AGND), U3.8 (PGND), U3.9 (PAD), U4.6 (AGND), U4.8 (PGND), U4.9 (PAD), U5.7 (GND), U6.6 (AGND), U6.8 (PGND), U6.9 (PAD), U7.6 (AGND), U7.8 (PGND), U7.9 (PAD), U9.7 (GND), U10.6 (AGND), U10.8 (PGND), U10.9 (PAD), U11.1 (GND), U12.1 (GND), U13.1 (GND), U14.1 (GND), U16.14 (SW1VSSSNS), U16.15 (GREF1), U16.32 (SW3VSSSNS), U16.48 (GNDREF), U16.57 (EPAD), U17.A4 (GND_3), U17.A8 (GND_4), U17.A13 (GND_1), U17.A25 (GND_2), U17.AA7 (GND_10), U17.AA10 (GND_5), U17.AA13 (GND_6), U17.AA16 (GND_7), U17.AA19 (GND_8), U17.AA22 (GND_9), U17.AB3 (GND_12), U17.AB24 (GND_11), U17.AD4 (GND_18), U17.AD7 (GND_19), U17.AD10 (GND_13), U17.AD13 (GND_14), U17.AD16 (GND_15), U17.AD19 (GND_16), U17.AD22 (GND_17), U17.AE1 (GND_20), U17.AE25 (GND_21), U17.B4 (GND_22), U17.C1 (GND_23), U17.C4 (GND_25), U17.C6 (GND_26), U17.C10 (GND_24), U17.D3 (GND_27), U17.D6 (GND_28), U17.D8 (GND_29), U17.E5 (GND_30), U17.E6 (GND_31), U17.E7 (GND_32), U17.F5 (GND_33), U17.F6 (GND_34), U17.F7 (GND_35), U17.F8 (GND_36), U17.G3 (GND_39), U17.G10 (GND_37), U17.G19 (GND_38), U17.H8 (GND_43), U17.H12 (GND_40), U17.H15 (GND_41), U17.H18 (GND_42), U17.J2 (GND_47), U17.J8 (GND_48), U17.J12 (GND_44), U17.J15 (GND_45), U17.J18 (GND_46), U17.K8 (GND_53), U17.K10 (GND_49), U17.K12 (GND_50), U17.K15 (GND_51), U17.K18 (GND_52), U17.L2 (GND_58), U17.L5 (GND_59), U17.L8 (GND_60), U17.L10 (GND_54), U17.L12 (GND_55), U17.L15 (GND_56), U17.L18 (GND_57), U17.M8 (GND_65), U17.M10 (GND_61), U17.M12 (GND_62), U17.M15 (GND_63), U17.M18 (GND_64), U17.N8 (GND_69), U17.N10 (GND_66), U17.N15 (GND_67), U17.N18 (GND_68), U17.P8 (GND_74), U17.P10 (GND_70), U17.P12 (GND_71), U17.P15 (GND_72), U17.P18 (GND_73), U17.R8 (GND_78), U17.R12 (GND_75), U17.R15 (GND_76), U17.R17 (GND_77), U17.T8 (GND_84), U17.T11 (GND_79), U17.T12 (GND_80), U17.T15 (GND_81), U17.T17 (GND_82), U17.T19 (GND_83), U17.U8 (GND_89), U17.U11 (GND_85), U17.U12 (GND_86), U17.U15 (GND_87), U17.U17 (GND_88), U17.U19 (GND_90), U17.V8 (GND_91), U17.V19 (GND_92), U17.W3 (GND_93), U17.W7 (GND_94), U17.W8 (GND_95), U17.W9 (GND_96), U17.W10 (GND_97), U17.W11 (GND_98), U17.W12 (GND_99), U17.W13 (GND_100), U17.W15 (GND_101), U17.W16 (GND_102), U17.W17 (GND_103), U17.W18 (GND_104), U17.W19 (GND_105), U17.Y5 (GND_106), U17.Y24 (GND_107), U19.3 (GND), U20.2 (GND), U22.A9 (VSS), U22.B1 (VSSQ), U22.B3 (VSS), U22.B9 (VSSQ), U22.D1 (VSSQ), U22.D8 (VSSQ), U22.E1 (VSS), U22.E2 (VSSQ), U22.E8 (VSSQ), U22.F9 (VSSQ), U22.G1 (VSSQ), U22.G8 (VSS), U22.G9 (VSSQ), U22.J2 (VSS), U22.J8 (VSS), U22.M1 (VSS), U22.M9 (VSS), U22.P1 (VSS), U22.P9 (VSS), U22.T1 (VSS), U22.T9 (VSS), U23.A9 (VSS), U23.B1 (VSSQ), U23.B3 (VSS), U23.B9 (VSSQ), U23.D1 (VSSQ), U23.D8 (VSSQ), U23.E1 (VSS), U23.E2 (VSSQ), U23.E8 (VSSQ), U23.F9 (VSSQ), U23.G1 (VSSQ), U23.G8 (VSS), U23.G9 (VSSQ), U23.J2 (VSS), U23.J8 (VSS), U23.M1 (VSS), U23.M9 (VSS), U23.P1 (VSS), U23.P9 (VSS), U23.T1 (VSS), U23.T9 (VSS), U24.A9 (VSS), U24.B1 (VSSQ), U24.B3 (VSS), U24.B9 (VSSQ), U24.D1 (VSSQ), U24.D8 (VSSQ), U24.E1 (VSS), U24.E2 (VSSQ), U24.E8 (VSSQ), U24.F9 (VSSQ), U24.G1 (VSSQ), U24.G8 (VSS), U24.G9 (VSSQ), U24.J2 (VSS), U24.J8 (VSS), U24.M1 (VSS), U24.M9 (VSS), U24.P1 (VSS), U24.P9 (VSS), U24.T1 (VSS), U24.T9 (VSS), U25.A9 (VSS), U25.B1 (VSSQ), U25.B3 (VSS), U25.B9 (VSSQ), U25.D1 (VSSQ), U25.D8 (VSSQ), U25.E1 (VSS), U25.E2 (VSSQ), U25.E8 (VSSQ), U25.F9 (VSSQ), U25.G1 (VSSQ), U25.G8 (VSS), U25.G9 (VSSQ), U25.J2 (VSS), U25.J8 (VSS), U25.M1 (VSS), U25.M9 (VSS), U25.P1 (VSS), U25.P9 (VSS), U25.T1 (VSS), U25.T9 (VSS), U26.4 (GND), U27.A1 (D12P), U27.A2 (D13P), U27.A3 (D14P), U27.A4 (D15P), U27.A5 (SYNCP), U27.A9 (OSTRP), U27.A12 (DACCLKP), U27.C2 (D11P), U27.C5 (GND), U27.C6 (GND), U27.C7 (GND), U27.C8 (GND), U27.C9 (GND), U27.D2 (D10P), U27.D8 (GND), U27.E2 (D9P), U27.E8 (GND), U27.F2 (D8P), U27.F6 (GND), U27.F7 (GND), U27.F8 (GND), U27.F9 (GND), U27.F14 (IOUTIP), U27.G2 (DATACLKP), U27.G6 (GND), U27.G7 (GND), U27.G8 (GND), U27.G9 (GND), U27.H2 (FRAMEP), U27.H6 (GND), U27.H7 (GND), U27.H8 (GND), U27.H9 (GND), U27.J2 (D7P), U27.J6 (GND), U27.J7 (GND), U27.J8 (GND), U27.J9 (GND), U27.J14 (IOUTQP), U27.K2 (D6P), U27.K8 (GND), U27.L2 (D5P), U27.L8 (GND)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
JTAG_NRST: R47.2, U17.C2 (~JTAG_RST)
JTAG_TMS: R45.2, U17.C3 (JTAG_TMS)
LCD_B0: J4.19 (B0), U17.P24 (DISP0_DAT0)
LCD_B1: J4.18 (B1), U17.P22 (DISP0_DAT1)
LCD_B2: J4.17 (B2), U17.P23 (DISP0_DAT2)
LCD_B3: J4.16 (B3), U17.P21 (DISP0_DAT3)
LCD_B4: J4.15 (B4), U17.P20 (DISP0_DAT4)
LCD_B5: J4.14 (B5), U17.R25 (DISP0_DAT5)
LCD_B6: J4.13 (B6), U17.R23 (DISP0_DAT6)
LCD_B7: J4.12 (B7), U17.R24 (DISP0_DAT7)
LCD_CLK: J4.37 (DCLK), U17.N19 (DI0_DISP_CLK)
LCD_ENABLE: J4.9 (DE), U17.N21 (DI0_PIN15)
LCD_G0: J4.27 (G0), U17.R22 (DISP0_DAT8)
LCD_G1: J4.26 (G1), U17.T25 (DISP0_DAT9)
LCD_G2: J4.25 (G2), U17.R21 (DISP0_DAT10)
LCD_G3: J4.24 (G3), U17.T23 (DISP0_DAT11)
LCD_G4: J4.23 (G4), U17.T24 (DISP0_DAT12)
LCD_G5: J4.22 (G5), U17.R20 (DISP0_DAT13)
LCD_G6: J4.21 (G6), U17.U25 (DISP0_DAT14)
LCD_G7: J4.20 (G7), U17.T22 (DISP0_DAT15)
LCD_HSYNC: J4.11 (HSYNC), U17.N25 (DI0_PIN2)
LCD_R0: J4.35 (R0), U17.T21 (DISP0_DAT16)
LCD_R1: J4.34 (R1), U17.U24 (DISP0_DAT17)
LCD_R2: J4.33 (R2), U17.V25 (DISP0_DAT18)
LCD_R3: J4.32 (R3), U17.U23 (DISP0_DAT19)
LCD_R4: J4.31 (R4), U17.U22 (DISP0_DAT20)
LCD_R5: J4.30 (R5), U17.T20 (DISP0_DAT21)
LCD_R6: J4.29 (R6), U17.V24 (DISP0_DAT22)
LCD_R7: J4.28 (R7), U17.W24 (DISP0_DAT23)
LCD_VSYNC: J4.10 (VSYNC), U17.N20 (DI0_PIN3)
unnamed: C1.2, U2.3 (VCC)
unnamed: C2.2, U1.3 (VCC)
unnamed: C3.2, U5.4 (SS)
unnamed: C4.2, U3.3 (VCC)
unnamed: C6.1, L5.1, U5.8 (PH)
unnamed: C6.2, U5.1 (BOOT)
unnamed: C7.1, R1.1
unnamed: C9.1, R1.2, U5.6 (COMP)
unnamed: C10.1, L1.1, U1.1 (SW)
unnamed: C10.2, U1.2 (BOOT)
unnamed: C11.1, L2.1, U2.1 (SW)
unnamed: C11.2, U2.2 (BOOT)
unnamed: C12.1, L3.1, U3.1 (SW)
unnamed: C12.2, U3.2 (BOOT)
unnamed: C14.1, L4.1, U4.1 (SW)
unnamed: C14.2, U4.2 (BOOT)
unnamed: C15.2, U6.3 (VCC)
unnamed: C19.1, C27.2, C37.2
unnamed: C40.1, L6.1, U6.1 (SW)
unnamed: C40.2, U6.2 (BOOT)
unnamed: C41.2, U7.3 (VCC)
unnamed: C45.2, U8.3 (VCC)
unnamed: C49.1, C49#2.1, C49#3.1, L7.1, U7.1 (SW)
unnamed: C49.2, C49#2.2, C49#3.2, U7.2 (BOOT)
unnamed: C50.1, L9.1, U9.8 (PH)
unnamed: C50.2, U9.1 (BOOT)
unnamed: C51.1, R18.1
unnamed: C52.1, L8.1, U8.1 (SW)
unnamed: C52.2, U8.2 (BOOT)
unnamed: C53.1, R18.2, U9.6 (COMP)
unnamed: C56.2, U10.3 (VCC)
unnamed: C70.1, L10.1, U10.1 (SW)
unnamed: C70.2, U10.2 (BOOT)
unnamed: C102.2, U16.52 (VCOREREF)
unnamed: C109.1, U16.49 (VCORE)
unnamed: C111.2, C112.1, U16.29 (VHALF)
unnamed: C113.1, C119.1, FB1.2
unnamed: C114.1, C120.1, FB2.2
unnamed: C115.1, C121.1, FB3.2
unnamed: C116.1, C122.1, FB4.2
unnamed: C117.1, C123.1, FB5.2
unnamed: C118.1, C124.1, FB6.2
unnamed: C127.1, C128.1, FB7.2
unnamed: C129.1, C130.1, FB8.2
unnamed: C147.1, C151.1
unnamed: C147.2, C148.1, C151.2, C152.1
unnamed: C148.2, C152.2
unnamed: C274.1, R65.1
unnamed: C277.1, R68.1, R72.2, R73.2, R74.2
unnamed: C291.1, L17.2, R86.2, U31.2 (IN+)
unnamed: C291.2, L18.2, R87.2, U31.3 (IN-)
unnamed: C295.2, U31.1 (VMID_IN)
unnamed: C298.1, R93.1
unnamed: C301.1, L20.1, R94.2
unnamed: C302.1, R97.1, R102.2, R103.2, R104.2
unnamed: C305.1, L20.2, R98.1, R99.1
unnamed: C308.1, R99.2
unnamed: C313.2, U27.E10 (DACVDD)
unnamed: C319.1, L21.2, R115.2, U35.2 (IN+)
unnamed: C319.2, L22.2, R116.2, U35.3 (IN-)
unnamed: C331.2, U35.1 (VMID_IN)
unnamed: C334.1, L23.1, R119.2
unnamed: C337.1, L23.2, R122.1, R123.1
unnamed: C339.1, R123.2
unnamed: C355.2, J11.1 (In), R135.2
unnamed: K1.1, Q1.3 (D)
unnamed: K2.1, Q2.3 (D)
unnamed: K3.1, Q3.3 (D)
unnamed: K4.1, Q4.3 (D)
unnamed: FB14.1, J3.5 (S1)
unnamed: J4.5 (GND), J4.36 (GND), J4.38 (GND), J4.48 (GND)
unnamed: J9.R4 (TCT), J9.R5 (RCT)
unnamed: K1.3, R69.2
unnamed: K1.4, K2.3
unnamed: K1.5, R70.2
unnamed: K1.8, R70.1
unnamed: K1.9, K2.10
unnamed: K1.10, R69.1
unnamed: K2.5, R71.1
unnamed: K2.8, R71.2
unnamed: K3.3, R90.2
unnamed: K3.4, K4.3
unnamed: K3.5, R91.2
unnamed: K3.8, R91.1
unnamed: K3.9, K4.10
unnamed: K3.10, R90.1
unnamed: K4.5, R92.1
unnamed: K4.8, R92.2
unnamed: L12.2, U16.8 (SW1ALX), U16.9 (SW1BLX)
unnamed: L13.2, U16.11 (SW1CLX)
unnamed: L14.2, U16.22 (SW2LX)
unnamed: L15.1, U16.35 (SW3BLX), U16.36 (SW3ALX)
unnamed: Q1.1 (G), R63.2, R66.1
unnamed: Q2.1 (G), R64.2, R67.1
unnamed: Q3.1 (G), R78.2, R82.1
unnamed: Q4.1 (G), R79.2, R83.1
unnamed: R2.2, R3.2, U1.4 (FB)
unnamed: R4.2, R5.2, U2.4 (FB)
unnamed: R6.2, R7.2, U3.4 (FB)
unnamed: R8.2, R9.2, U4.4 (FB)
unnamed: R10.2, R11.1, U5.5 (VSNS)
unnamed: R12.2, R13.2, U6.4 (FB)
unnamed: R14.2, R15.2, U7.4 (FB)
unnamed: R16.2, R17.2, U8.4 (FB)
unnamed: R19.2, R20.1, U9.5 (VSNS)
unnamed: R21.2, R22.2, U10.4 (FB)
unnamed: R23.2, R24.2, U16.56 (PWRON)
unnamed: R24.1, R25.2, R26.2
unnamed: R27.2, U16.53 (SDA)
unnamed: R28.2, U16.54 (SCL)
unnamed: R29.2, U16.5 (ICTEST)
unnamed: R30.1, U16.2 (SDWNB)
unnamed: R33.2, R34.2, U16.47 (VDDOTP)
unnamed: R37.1, R38.1
unnamed: R56.2, U22.L8 (ZQ)
unnamed: R57.2, U23.L8 (ZQ)
unnamed: R58.2, U17.AE17 (ZQPAD)
unnamed: R59.2, U24.L8 (ZQ)
unnamed: R60.2, U25.L8 (ZQ)
unnamed: R61.2, U26.3 (~WP)
unnamed: R62.2, U26.7 (~HOLD)
unnamed: R72.1, U28.3 (VIN+)
unnamed: R73.1, U29.3 (VIN+)
unnamed: R74.1, U30.3 (VIN+)
unnamed: R80.1, R81.1, R84.1, R85.2
unnamed: R80.2, U29.6 (VOUT)
unnamed: R81.2, U30.6 (VOUT)
unnamed: R88.1, R89.1, U31.4 (PATHSEL)
unnamed: R94.1, U31.6 (VO1)
unnamed: R95.2, R96.2, U31.14 (VREF)
unnamed: R98.2, U31.9 (VIN+)
unnamed: R100.1, R101.1, R106.2, U31.12 (VIN-)
unnamed: R96.1, R100.2, U31.15 (VMID_OUT)
unnamed: R102.1, U32.3 (VIN+)
unnamed: R103.1, U33.3 (VIN+)
unnamed: R104.1, U34.3 (VIN+)
unnamed: R107.1, R108.1, R109.1, R111.2
unnamed: R108.2, U33.6 (VOUT)
unnamed: R109.2, U34.6 (VOUT)
unnamed: R110.1, R112.2
unnamed: R110.2, U27.J11 (AVDD)
unnamed: R117.1, R118.1, U35.4 (PATHSEL)
unnamed: R119.1, U35.6 (VO1)
unnamed: R120.2, R121.2, U35.14 (VREF)
unnamed: R121.1, R124.2, U35.15 (VMID_OUT)
unnamed: R122.2, U35.9 (VIN+)
unnamed: R124.1, R125.1, R127.2, U35.12 (VIN-)
unnamed: R125.2, R126.2, U35.11 (VOUT)
unnamed: U28.1 (REF), U29.1 (REF), U30.1 (REF)
unnamed: U32.4 (VS-), U33.4 (VS-), U34.4 (VS-)
OTG_VBUS: C353.1, FB15.2, U17.E9 (USB_OTG_VBUS), U19.6 (OUT), U19.8 (OUT)
PMIC_INT_B: R31.1, U16.1 (INTB)
PMIC_ON_REQ: R25.1, U17.D11 (PMIC_ON_REQ)
PMIC_STDBY: U16.4 (STANDBY), U17.F11 (PMIC_STBY_REQ)
TAMPER: R132.1, U17.E11 (TAMPER)
V: C106.1, R32.2
VCOREDIG: R34.1, U16.51 (VCOREDIG)
VDD_ARM_IN: C84.2, C88.2, C92.2, C97.2, C186.1, C187.2, C190.1, C191.2, C194.1, C195.2, C198.1, C199.2, C202.1, C203.2, C206.1, C207.2, L12.1, U16.6 (SW1FB), U17.H14 (VDDARM_IN_1), U17.J14 (VDDARM_IN_2), U17.K9 (VDDARM23_IN_1), U17.K14 (VDDARM_IN_3), U17.L9 (VDDARM23_IN_2), U17.L14 (VDDARM_IN_4), U17.M9 (VDDARM23_IN_3), U17.M14 (VDDARM_IN_5), U17.N9 (VDDARM23_IN_4), U17.N14 (VDDARM_IN_6), U17.P9 (VDDARM23_IN_5), U17.P14 (VDDARM_IN_7), U17.R9 (VDDARM23_IN_6), U17.R14 (VDDARM_IN_8), U17.T9 (VDDARM23_IN_7), U17.U9 (VDDARM23_IN_8)
VDD_SOC_IN: C100.2, C101.2, C103.2, C188.1, C189.2, C192.1, C193.2, C196.1, C197.2, C200.1, C201.2, C204.1, C205.2, C208.1, C209.2, L13.1, U16.13 (SW1CFB), U17.H16 (VDDSOC_IN_1), U17.J16 (VDDSOC_IN_2), U17.K16 (VDDSOC_IN_3), U17.L16 (VDDSOC_IN_4), U17.M16 (VDDSOC_IN_5), U17.N16 (VDDSOC_IN_6), U17.P16 (VDDSOC_IN_7), U17.R16 (VDDSOC_IN_8), U17.T16 (VDDSOC_IN_9), U17.U16 (VDDSOC_IN_10)
VIN_ACDC: C8.1, C13.1, C17.2, C22.1, C22#2.1, C24.2, C26.1, C28.1, C31.1, C33.1, C35.1, C36.2, C38.1, C43.1, C44.2, C57.2, C57#2.2, C60.1, C61.2, C64.1, C65.2, C72.1, C73.2, C75.1, D1.2 (A2), J1.3, J1.4, TP1.1, U1.5 (EN/SYNC), U1.7 (VIN), U2.5 (EN/SYNC), U2.7 (VIN), U3.5 (EN/SYNC), U3.7 (VIN), U4.5 (EN/SYNC), U4.7 (VIN), U5.2 (VIN), U5.3 (EN), U6.5 (EN/SYNC), U6.7 (VIN), U7.5 (EN/SYNC), U7.7 (VIN), U8.5 (EN/SYNC), U8.7 (VIN), U9.2 (VIN), U9.3 (EN), U10.5 (EN/SYNC), U10.7 (VIN)

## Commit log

2021-04-30 WIP : Update.
2021-04-30 WIP: update
2021-04-30 initial read me.
2021-05-01 WIP.
2021-07-29 Update.
2022-05-27 adding initial concept.
2023-09-22 commit message
